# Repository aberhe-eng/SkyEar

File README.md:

# SkyEar

**A pocket radio that listens to lightning thousands of miles away.**

Lightning strikes somewhere on Earth dozens of times every second, and every strike gives off a burst of very-low-frequency (VLF) radio. SkyEar picks those bursts up with a wire antenna, cleans them up, and plays them through headphones. You hear distant storms as crackling ("sferics"), and sometimes as eerie falling whistles ("whistlers"): lightning signals that went out into space, followed Earth's magnetic field, and came back down.

I'm building it for [Hack Club Half Life](https://halflife.hackclub.com) (Week 1: PCB design).

## How it works

SkyEar is a fully analog circuit: two op-amp chips, one headphone amp chip, and a 9 V battery. The signal goes through it in this order:

| Stage | Part | What it does |
| --- | --- | --- |
| Antenna input | J2, R4, D3, D4 | A wire antenna plus a ground stake. The diodes dump static from the antenna safely into the power rails. |
| Buffer | U1A (TL072), R5 = 10 MΩ | A short antenna acts like a tiny capacitor (~10–30 pF), so it can barely push any current. The 10 MΩ input and a JFET op-amp copy the signal without draining it. |
| Hum filter | U1B, C6, C7, R6, R7 | 2nd-order high-pass at ~625 Hz. Power lines put out 60 Hz hum that's way louder than lightning on another continent, so this cuts it. |
| Gain | U2A, R8, R9 | Amplifies by 1 + 100k / 3.3k ≈ 31. |
| High-frequency filter | U2B, R10, R11, C10, C11 | 2nd-order low-pass at ~10.7 kHz. Cuts hiss, AM radio, and the Navy's VLF transmitters (~20–25 kHz). |
| Headphone amp | U3 (LM386), RV1 | Another 20x, with a volume knob. About 620x total from antenna to ears. |
| Line out | J4 | A clean copy of the audio for recording, or for my later Half Life projects. |
| Power | J1, SW1, D1, R2, R3 | 9 V battery with reverse-polarity protection. R2/R3 make a ~4.35 V "virtual ground" (VREF) so the op-amps can swing both ways on one battery. |

The filter cutoffs come from the standard formulas:

- Input: f = 1 / (2π · 10 MΩ · 30 pF) ≈ 530 Hz
- Hum filter: f = 1 / (2π · 10 nF · √(18 kΩ · 36 kΩ)) ≈ 625 Hz
- Low-pass: f = 1 / (2π · 10 kΩ · √(2.2 nF · 1 nF)) ≈ 10.7 kHz

## Schematic

The full KiCad project is in [`pcb/`](pcb/). Open `pcb/skyear.kicad_pro` in KiCad 10 (the schematic alone also opens in KiCad 8 and 9). A PDF copy is at [`pcb/skyear_schematic.pdf`](pcb/skyear_schematic.pdf).

### Block by block

**Power:** 9 V battery → slide switch → 1N5817 Schottky diode (blocks a backwards battery, only ~0.3 V drop) → +9V rail, with a power LED.

**Virtual ground:** two 10k resistors split the battery to ~4.35 V so every op-amp signal can swing above and below it.

**Antenna input + buffer:** R5 is 10 MΩ so the antenna's tiny signal isn't loaded down, and U1A just copies it.

C5 (22 pF) is marked "do not fit". It only gets soldered if AM radio leaks in.

**Hum filter:** R7 (36k) is exactly twice R6 (18k), which gives a flat Butterworth response with no bump at the cutoff.

**Gain stage:** x31. C9 keeps DC from being amplified and C8 starts rolling off the highs.

**High-frequency filter:** cuts everything above ~10.7 kHz.

**Line out:** a DC-blocked copy of the audio on a 2-pin header.

**Headphone amp:** LM386 at x20. R14 + C17 keep it from oscillating, C18 blocks DC from the headphones, and R15 limits the max volume. Tip and ring are tied together so both ears get the signal.

### Checks

KiCad's Electrical Rules Checker: **0 errors**. The 2 warnings are KiCad 10 noticing that the LED and potentiometer symbols have newer artwork in its library; the pins are identical.

Every part has a footprint assigned:

+9V and GND are in a "Power" net class so they get thicker 0.6 mm tracks on the PCB (signals get 0.3 mm):

## PCB

| | |
| --- | --- |
| Size | 90 × 64 mm, 2 layers, 1.6 mm FR-4, 4 × M3 mounting holes |
| Tracks | 0.3 mm signal, 0.6 mm for +9V and GND, 0.25 mm clearance |
| Ground | GND pour on both layers, stitched together with vias |
| Checks | KiCad DRC: **0 errors, 0 unconnected pads, 0 schematic mismatches** ([report](pcb/skyear_drc_report.rpt)) |

The 14 DRC warnings are all expected: 13 are connector bodies (terminal blocks, switch, jack, LED) that hang over the board edge on purpose, and 1 is the headphone jack footprint, whose pin slots were widened from 0.4 mm to 0.6 mm because JLCPCB can't make plated slots narrower than 0.5 mm.

### Layout

- **Signal flows left to right.** Antenna in on the left edge, then the buffer (U1), hum filter, gain stage (U2) and low-pass filter across the top. The headphone amp (U3), volume knob and jack are along the bottom right.
- **The antenna input is kept tiny.** Everything touching the 10 MΩ input node (R4, R5, D3, D4, C5) sits right next to U1 pin 3, because that node picks up hum if its traces are long.
- **The headphone amp is far from the input.** The LM386's output (the loudest signal on the board) is in the opposite corner from the antenna, so it can't feed back into the input and squeal.
- **Every chip has its 100 nF decoupling cap next to its power pin** (C19 for U1, C20 for U2, C15 for U3).
- **Controls are on the edges.** Battery and antenna terminals on the left, power switch and volume on the bottom, headphone jack and line out on the right.
- Routed with [Freerouting](https://github.com/freerouting/freerouting), then GND pours on both layers.

| Front copper | Back copper |
| --- | --- |
|  |  |

The front/back images are rendered straight from the Gerber files, so they show exactly what gets manufactured. The 3D views are from KiCad; the volume pot has no 3D model in KiCad's library, so only its pads show.

### Ordering the boards

[`pcb/skyear_gerbers_jlcpcb.zip`](pcb/skyear_gerbers_jlcpcb.zip) is ready to upload at [jlcpcb.com/quote](https://jlcpcb.com/quote) (2 layers, 1.6 mm, 5 pcs, any color). The individual Gerber and drill files are in [`pcb/gerbers/`](pcb/gerbers/). The board file is `pcb/skyear.kicad_pcb` (KiCad 10).

## Specs

| | |
| --- | --- |
| Frequency range | ~600 Hz to ~10.7 kHz |
| Power | One 9 V battery, ~10–15 mA |
| Input | Wire antenna + ground stake, 10 MΩ input resistance |
| Outputs | 3.5 mm headphones (with volume), 2-pin line out |
| Parts | 100% through-hole, all chips socketed |
| Board | 2 layers, 90 × 64 mm, 4 × M3 mounting holes |

## Parts list

[`bom.csv`](bom.csv) has every part with its quantity, real DigiKey price and part number, plus the PCBs from JLCPCB.

- Parts from DigiKey: **$29.67** (34 lines, including spares of the cheap parts)
- 5 PCBs from JLCPCB: **$2.00**
- **Parts total: $31.67**, before tax and shipping. That's inside the Tier 2 budget ($65).

Not on the list: a 9 V battery (any store) and the antenna wire + ground stake (already owned).

There's no firmware: SkyEar is entirely analog.

## Status

- [x] Circuit design and filter math
- [x] Schematic (KiCad), 0 errors in the electrical rules check
- [x] Price the BOM (Tier 2)
- [x] PCB layout and routing, 0 DRC errors
- [x] Gerber files for fabrication
- [ ] Build week: solder and test
- [ ] Field test: record real sferics and post the audio here

## Safety

- **Never set up the antenna when there are storms nearby.** If you can hear thunder, pack up. SkyEar listens to lightning far away, never close.
- **Battery power only.** Never connect it to a wall adapter.
- **Turn the volume to zero before putting headphones on.**
- Keep antennas far away from overhead power lines.

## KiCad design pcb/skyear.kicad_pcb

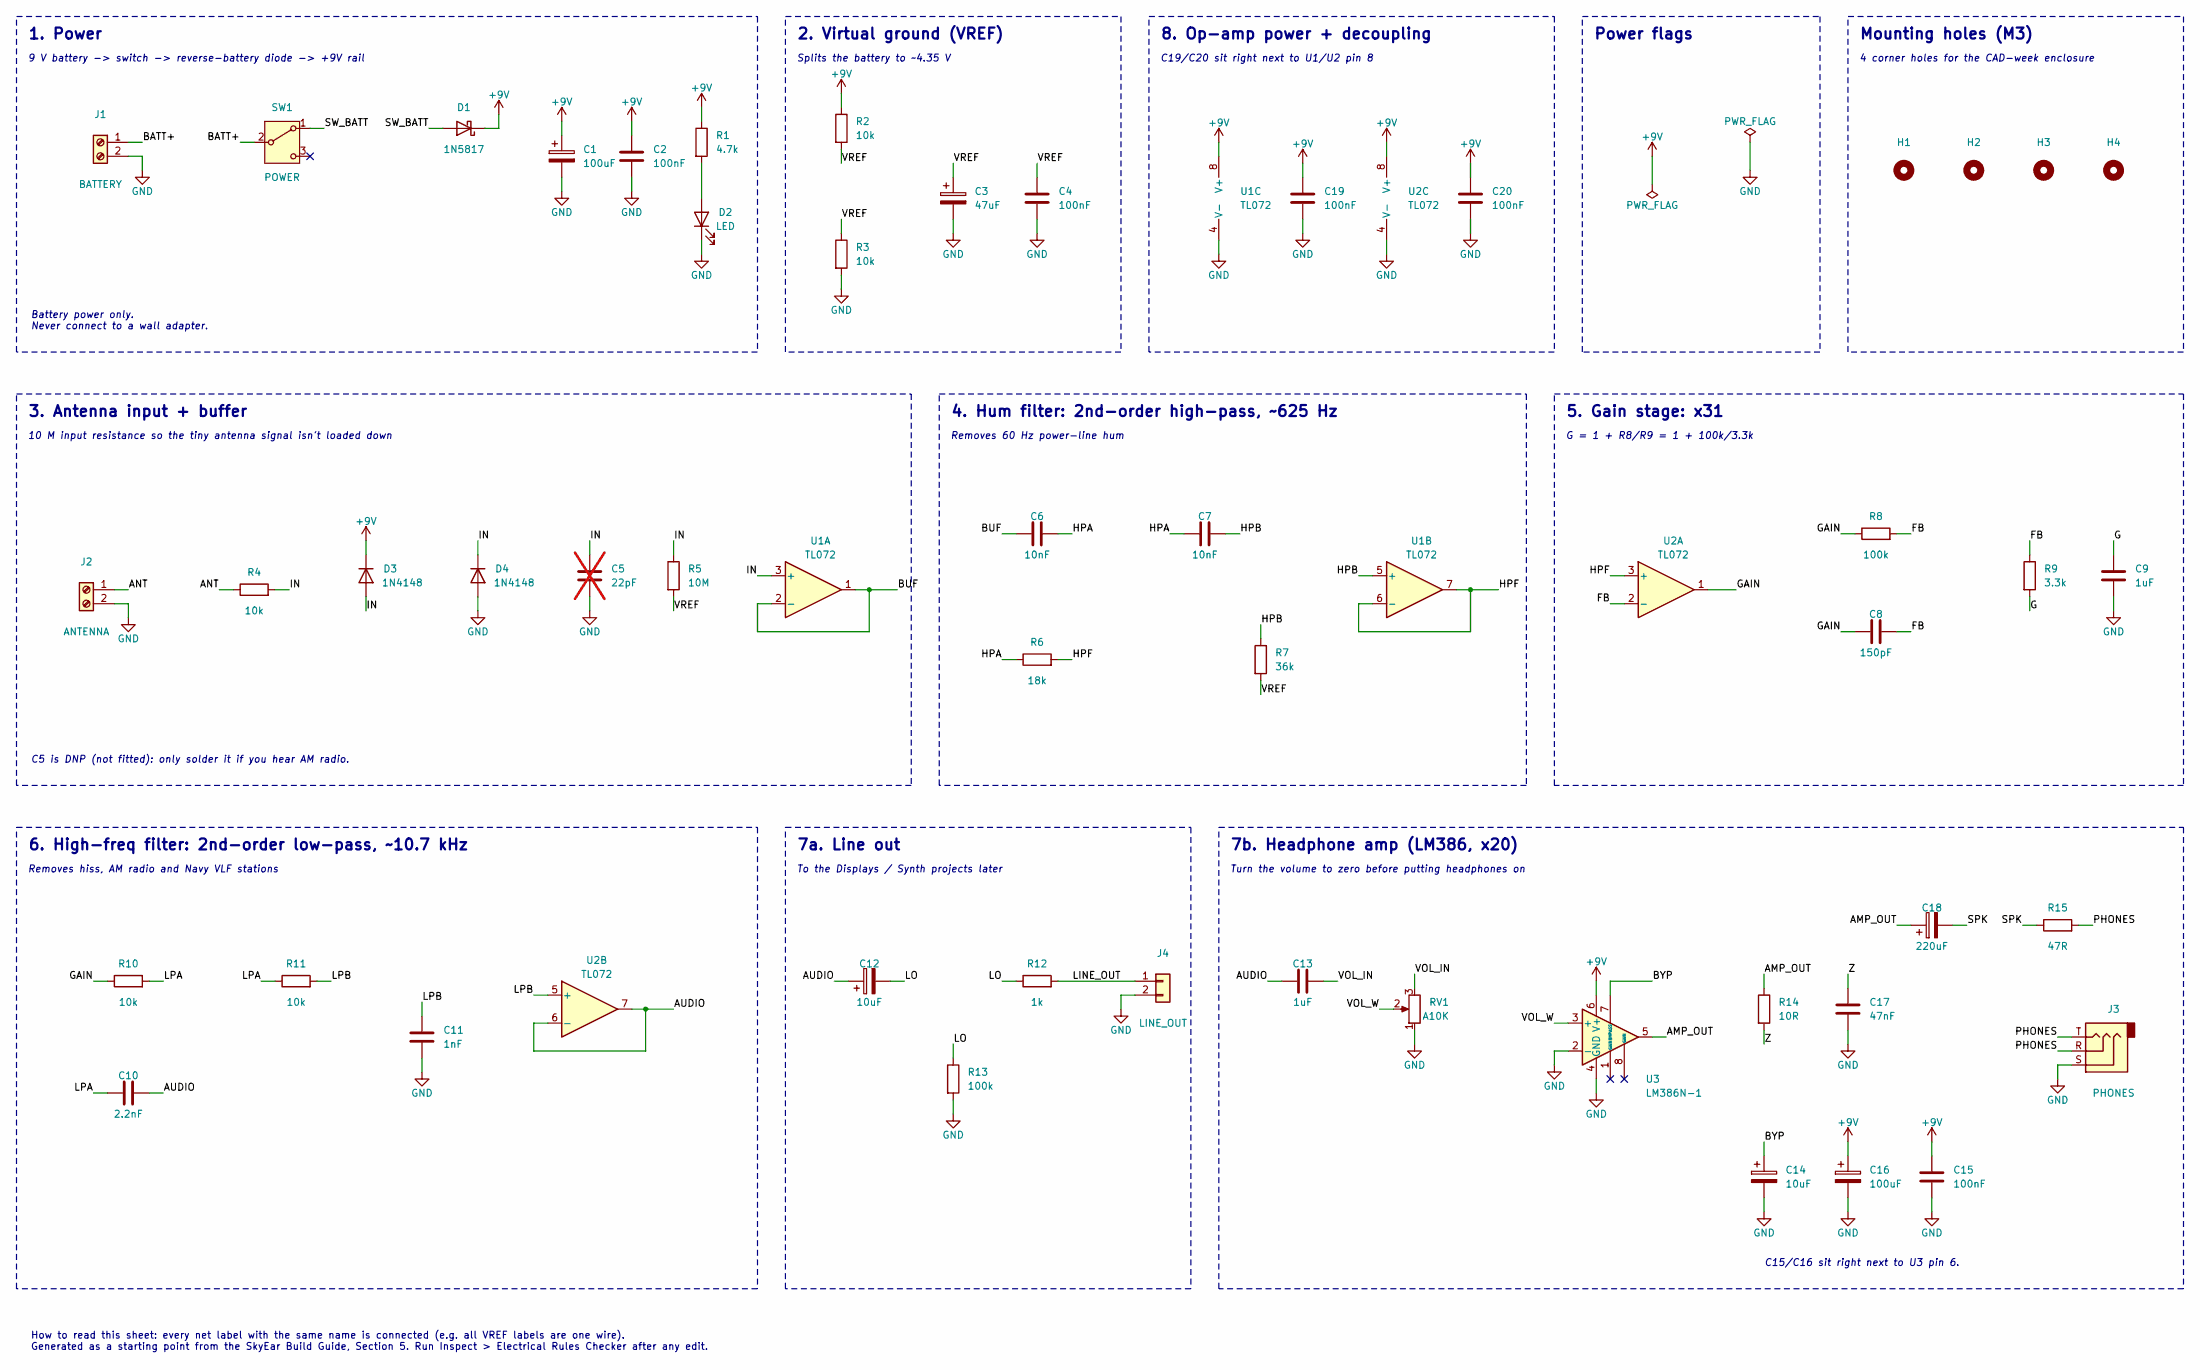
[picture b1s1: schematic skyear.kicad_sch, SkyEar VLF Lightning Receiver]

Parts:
C1, C16: 100uF; CP_Radial_D6.3mm_P2.50mm
C2, C4, C15, C19, C20: 100nF; C_Disc_D5.0mm_W2.5mm_P5.00mm
C3: 47uF; CP_Radial_D6.3mm_P2.50mm
C5: 22pF; C_Disc_D5.0mm_W2.5mm_P5.00mm; not fitted
C6, C7: 10nF; C_Disc_D5.0mm_W2.5mm_P5.00mm
C8: 150pF; C_Disc_D5.0mm_W2.5mm_P5.00mm
C9, C13: 1uF; C_Disc_D5.0mm_W2.5mm_P5.00mm
C10: 2.2nF; C_Disc_D5.0mm_W2.5mm_P5.00mm
C11: 1nF; C_Disc_D5.0mm_W2.5mm_P5.00mm
C12, C14: 10uF; CP_Radial_D5.0mm_P2.00mm
C17: 47nF; C_Disc_D5.0mm_W2.5mm_P5.00mm
C18: 220uF; CP_Radial_D8.0mm_P3.50mm
D1: 1N5817; D_DO-41_SOD81_P10.16mm_Horizontal
D2: LED; LED_D5.0mm
D3, D4: 1N4148; D_DO-35_SOD27_P7.62mm_Horizontal
H1, H2, H3, H4: MountingHole; MountingHole_3.2mm_M3
J1: BATTERY; TerminalBlock_Phoenix_MKDS-1,5-2-5.08_1x02_P5.08mm_Horizont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; MPN Phoenix MKDS 1,5/2-5,08 (or same 5.08 m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
J2: ANTENNA; TerminalBlock_Phoenix_MKDS-1,5-2-5.08_1x02_P5.08mm_Horizont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; MPN Phoenix MKDS 1,5/2-5,08 (or same 5.08 m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
J3: PHONES; Jack_3.5mm_CUI_SJ1-3523N_Horizontal; MPN CUI SJ1-3523N
J4: LINE_OUT; PinHeader_1x02_P2.54mm_Vertical
R1: 4.7k; R_Axial_DIN0207_L6.3mm_D2.5mm_P10.16mm_Horizontal
R2, R3, R4, R10, R11: 10k; R_Axial_DIN0207_L6.3mm_D2.5mm_P10.16mm_Horizontal
R5: 10M; R_Axial_DIN0207_L6.3mm_D2.5mm_P10.16mm_Horizontal
R6: 18k; R_Axial_DIN0207_L6.3mm_D2.5mm_P10.16mm_Horizontal
R7: 36k; R_Axial_DIN0207_L6.3mm_D2.5mm_P10.16mm_Horizontal
R8, R13: 100k; R_Axial_DIN0207_L6.3mm_D2.5mm_P10.16mm_Horizontal
R9: 3.3k; R_Axial_DIN0207_L6.3mm_D2.5mm_P10.16mm_Horizontal
R12: 1k; R_Axial_DIN0207_L6.3mm_D2.5mm_P10.16mm_Horizontal
R14: 10R; R_Axial_DIN0207_L6.3mm_D2.5mm_P10.16mm_Horizontal
R15: 47R; R_Axial_DIN0207_L6.3mm_D2.5mm_P10.16mm_Horizontal
RV1: A10K; Potentiometer_Alps_RK09K_Single_Vertical; MPN Alps RK09K series, 10k audio (A) taper
SW1: POWER; SW_Slide_SPDT_Angled_CK_OS102011MA1Q; MPN C&K OS102011MA1QN1 (right-angle)
U1, U2: TL072; DIP-8_W7.62mm_Socket
U3: LM386N-1; DIP-8_W7.62mm_Socket

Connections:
+9V: C1.1, C2.1, C15.1, C16.1, C19.1, C20.1, D1.1 (K), D3.1 (K), R1.1, R2.1, U1.8 (V+), U2.8 (V+), U3.6 (V+)
/AMP_OUT: C18.1, R14.1, U3.5
/ANT: J2.1, R4.1
/AUDIO: C10.2, C12.1, C13.1, U2.6 (-), U2.7
/BATT+: J1.1, SW1.2 (B)
/BUF: C6.1, U1.1, U1.2 (-)
/BYP: C14.1, U3.7 (BYPASS)
/FB: C8.2, R8.2, R9.1, U2.2 (-)
/G: C9.1, R9.2
/GAIN: C8.1, R8.1, R10.1, U2.1
/HPA: C6.2, C7.1, R6.1
/HPB: C7.2, R7.1, U1.5 (+)
/HPF: R6.2, U1.6 (-), U1.7, U2.3 (+)
/IN: C5.1, D3.2 (A), D4.1 (K), R4.2, R5.1, U1.3 (+)
/LINE_OUT: J4.1, R12.2
/LO: C12.2, R12.1, R13.1
/LPA: C10.1, R10.2, R11.1
/LPB: C11.1, R11.2, U2.5 (+)
/PHONES: J3.R, J3.T, R15.2
/SPK: C18.2, R15.1
/SW_BATT: D1.2 (A), SW1.1 (A)
/VOL_IN: C13.2, RV1.3
/VOL_W: RV1.2, U3.3 (+)
/VREF: C3.1, C4.1, R2.2, R3.1, R5.2, R7.2
/Z: C17.1, R14.2
GND: C1.2, C2.2, C3.2, C4.2, C5.2, C9.2, C11.2, C14.2, C15.2, C16.2, C17.2, C19.2, C20.2, D2.1 (K), D4.2 (A), J1.2, J2.2, J3.S, J4.2, R3.2, R13.2, RV1.1, U1.4 (V-), U2.4 (V-), U3.2 (-), U3.4 (GND)
unnamed: D2.2 (A), R1.2

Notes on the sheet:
1. Power
9 V battery -> switch -> reverse-battery diode -> +9V rail
Battery power only. Never connect to a wall adapter.
2. Virtual ground (VREF)
Splits the battery to ~4.35 V
8. Op-amp power + decoupling
C19/C20 sit right next to U1/U2 pin 8
Power flags
Mounting holes (M3)
4 corner holes for the CAD-week enclosure
3. Antenna input + buffer
10 M input resistance so the tiny antenna signal isn't loaded down
C5 is DNP (not fitted): only solder it if you hear AM radio.
4. Hum filter: 2nd-order high-pass, ~625 Hz
Removes 60 Hz power-line hum
5. Gain stage: x31
G = 1 + R8/R9 = 1 + 100k/3.3k
6. High-freq filter: 2nd-order low-pass, ~10.7 kHz
Removes hiss, AM radio and Navy VLF stations
7a. Line out
To the Displays / Synth projects later
7b. Headphone amp (LM386, x20)
Turn the volume to zero before putting headphones on
C15/C16 sit right next to U3 pin 6.
How to read this sheet: every net label with the same name is connected (e.g. all VREF labels are one wire). Generated as a starting point from the SkyEar Build Guide, Section 5. Run Inspect > Electrical Rules Checker after any edit.

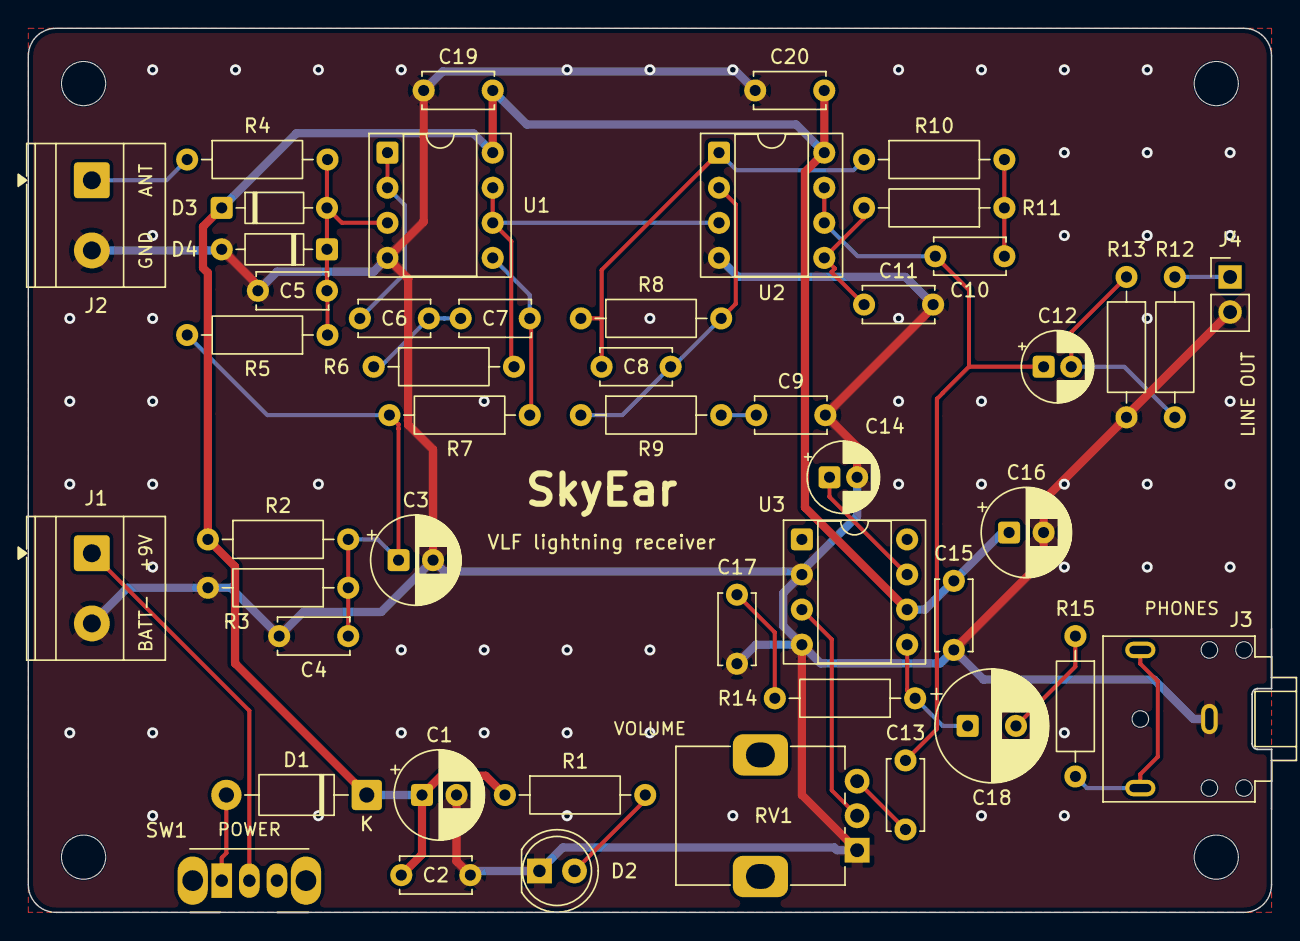
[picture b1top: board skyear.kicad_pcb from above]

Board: 2 copper layers, 90.0 x 64.0 mm, 52 parts (0 on the bottom side), 27 nets.

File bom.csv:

Part,Qty,Unit price (USD),Total (USD),Vendor,Link,Refs,Manufacturer,MPN,Vendor PN
Resistor 4.7k ohm 1/4W - YAGEO MFR-25FBF52-4K7,2,0.11,0.22,DigiKey,https://www.digikey.com/en/products/result?keywords=MFR-25FB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,R1,YAGEO,MFR-25FBF52-4K7,MFR-25FBF52-4K7-ND
Resistor 10k ohm 1/4W - YAGEO MFR-25FBF52-10K,10,0.042,0.42,DigiKey,https://www.digikey.com/en/products/result?keywords=10.0KXBK-ND,"R2,R3,R4,R10,R11",YAGEO,MFR-25FBF52-10K,10.0KXBK-ND
Resistor 10M ohm (10 megohm) 1/4W - Stackpole CF14JT10M0,2,0.10,0.20,DigiKey,https://www.digikey.com/en/products/result?keywords=CF14JT10M0CT-ND,R5,Stackpole,CF14JT10M0,CF14JT10M0CT-ND
Resistor 18k ohm 1/4W - YAGEO MFR-25FBF52-18K,2,0.10,0.20,DigiKey,https://www.digikey.com/en/products/result?keywords=MFR-25FB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,R6,YAGEO,MFR-25FBF52-18K,MFR-25FBF52-18K-ND
Resistor 36k ohm 1/4W - YAGEO MFR-25FBF52-36K,2,0.10,0.20,DigiKey,https://www.digikey.com/en/products/result?keywords=13-MFR-2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,R7,YAGEO,MFR-25FBF52-36K,13-MFR-25FBF52-36K-ND
Resistor 100k ohm 1/4W - YAGEO MFR-25FBF52-100K,3,0.10,0.30,DigiKey,https://www.digikey.com/en/products/result?keywords=100KXBK-ND,"R8,R13",YAGEO,MFR-25FBF52-100K,100KXBK-ND
Resistor 3.3k ohm 1/4W - YAGEO MFR-25FBF52-3K3,2,0.10,0.20,DigiKey,https://www.digikey.com/en/products/result?keywords=MFR-25FB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,R9,YAGEO,MFR-25FBF52-3K3,MFR-25FBF52-3K3-ND
Resistor 1k ohm 1/4W - YAGEO MFR-25FBF52-1K,2,0.10,0.20,DigiKey,https://www.digikey.com/en/products/result?keywords=1.00KXBK-ND,R12,YAGEO,MFR-25FBF52-1K,1.00KXBK-ND
Resistor 10 ohm 1/4W - YAGEO MFR-25FBF52-10R,2,0.10,0.20,DigiKey,https://www.digikey.com/en/products/result?keywords=10.0XBK-ND,R14,YAGEO,MFR-25FBF52-10R,10.0XBK-ND
Resistor 47 ohm 1/4W - YAGEO MFR-25FBF52-47R,2,0.10,0.20,DigiKey,https://www.digikey.com/en/products/result?keywords=MFR-25FB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,R15,YAGEO,MFR-25FBF52-47R,MFR-25FBF52-47R-ND
Electrolytic capacitor 100uF 25V - Panasonic ECA-1EM101I,3,0.35,1.05,DigiKey,https://www.digikey.com/en/products/result?keywords=10-ECA-1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,"C1,C16",Panasonic,ECA-1EM101I,10-ECA-1EM101ICT-ND
Ceramic capacitor 100nF 50V - TDK FG28X7R1H104KNT00,10,0.135,1.35,DigiKey,https://www.digikey.com/en/products/result?keywords=445-FG28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,"C2,C4,C15,C19,C20",TDK,FG28X7R1H104KNT00,445-FG28X7R1H104KNT00-ND
Electrolytic capacitor 47uF 50V - Panasonic ECA-1HM470,2,0.33,0.66,DigiKey,https://www.digikey.com/en/products/result?keywords=P5181-ND,C3,Panasonic,ECA-1HM470,P5181-ND
"Ceramic capacitor 22pF 100V (C5 spare, not fitted) - TDK FG28C0G2A220JNT00",1,0.26,0.26,DigiKey,https://www.digikey.com/en/products/result?keywords=445-175549-ND,C5,TDK,FG28C0G2A220JNT00,445-175549-ND
Ceramic capacitor 10nF 50V C0G - TDK FG28C0G1H103JNT00,3,0.35,1.05,DigiKey,https://www.digikey.com/en/products/result?keywords=FG28C0G1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,"C6,C7",TDK,FG28C0G1H103JNT00,FG28C0G1H103JNT00-ND
Ceramic capacitor 150pF 50V C0G - TDK FG28C0G1H151JNT00,2,0.22,0.44,DigiKey,https://www.digikey.com/en/products/result?keywords=445-181753-ND,C8,TDK,FG28C0G1H151JNT00,445-181753-ND
Ceramic capacitor 1uF 25V - TDK FG28X7R1E105KRT00,3,0.31,0.93,DigiKey,https://www.digikey.com/en/products/result?keywords=445-181761-ND,"C9,C13",TDK,FG28X7R1E105KRT00,445-181761-ND
Ceramic capacitor 2.2nF 50V C0G - TDK FG28C0G1H222JNT00,2,0.27,0.54,DigiKey,https://www.digikey.com/en/products/result?keywords=445-FG28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,C10,TDK,FG28C0G1H222JNT00,445-FG28C0G1H222JNT00-ND
Ceramic capacitor 1nF 50V C0G - TDK FG28C0G1H102JNT00,2,0.25,0.50,DigiKey,https://www.digikey.com/en/products/result?keywords=445-FG28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,C11,TDK,FG28C0G1H102JNT00,445-FG28C0G1H102JNT00-ND
Electrolytic capacitor 10uF 50V - KEMET ESK106M050AC3AA,3,0.19,0.57,DigiKey,https://www.digikey.com/en/products/result?keywords=399-6599-ND,"C12,C14",KEMET,ESK106M050AC3AA,399-6599-ND
Ceramic capacitor 47nF 50V - TDK FG28X7R1H473KNT00,2,0.23,0.46,DigiKey,https://www.digikey.com/en/products/result?keywords=445-FG28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,C17,TDK,FG28X7R1H473KNT00,445-FG28X7R1H473KNT00-ND
Electrolytic capacitor 220uF 25V - Nichicon UVZ1E221MPD,2,0.44,0.88,DigiKey,https://www.digikey.com/en/products/result?keywords=493-1302-ND,C18,Nichicon,UVZ1E221MPD,493-1302-ND
Schottky diode 1N5817 (reverse-battery protection) - onsemi 1N5817G,2,0.67,1.34,DigiKey,https://www.digikey.com/en/products/result?keywords=1N5817GOS-ND,D1,onsemi,1N5817G,1N5817GOS-ND
Red 5 mm LED (power light) - Kingbright WP7113ID,2,0.21,0.42,DigiKey,https://www.digikey.com/en/products/result?keywords=754-1264-ND,D2,Kingbright,WP7113ID,754-1264-ND
Diode 1N4148 (antenna input protection) - onsemi 1N4148,4,0.10,0.40,DigiKey,https://www.digikey.com/en/products/result?keywords=1N4148FS-ND,"D3,D4",onsemi,1N4148,1N4148FS-ND
"TL072 dual JFET op-amp, DIP-8 - Texas Instruments TL072ACP",3,1.50,4.50,DigiKey,https://www.digikey.com/en/products/result?keywords=296-7190-5-ND,"U1,U2",Texas Instruments,TL072ACP,296-7190-5-ND
"LM386 headphone amplifier, DIP-8 - Texas Instruments LM386N-1/NOPB",2,1.18,2.36,DigiKey,https://www.digikey.com/en/products/result?keywords=296-44414-5-ND,U3,Texas Instruments,LM386N-1/NOPB,296-44414-5-ND
"2-pin screw terminal 5.08 mm (battery, antenna) - Phoenix Contact 1715721",2,1.16,2.32,DigiKey,https://www.digikey.com/en/products/result?keywords=277-1263-ND,"J1,J2",Phoenix Contact,1715721,277-1263-ND
3.5 mm headphone jack - Same Sky (CUI) SJ1-3523N,1,1.12,1.12,DigiKey,https://www.digikey.com/en/products/result?keywords=CP1-3523N-ND,J3,Same Sky (CUI),SJ1-3523N,CP1-3523N-ND
2-pin header 2.54 mm (line out) - Sullins PREC002SAAN-RC,1,0.10,0.10,DigiKey,https://www.digikey.com/en/products/result?keywords=35-PREC0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,J4,Sullins,PREC002SAAN-RC,35-PREC002SAAN-RC-ND
Slide switch SPDT right-angle (power) - C&K OS102011MA1QN1,1,0.75,0.75,DigiKey,https://www.digikey.com/en/products/result?keywords=CKN9559-ND,SW1,C&K,OS102011MA1QN1,CKN9559-ND
10k potentiometer (volume) - Alps Alpine RK09K1130AP5,1,1.70,1.70,DigiKey,https://www.digikey.com/en/products/result?keywords=4809-RK0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,RV1,Alps Alpine,RK09K1130AP5,4809-RK09K1130AP5-ND
9V battery snap clip - Keystone 232,1,0.66,0.66,DigiKey,https://www.digikey.com/en/products/result?keywords=36-232-ND,J1,Keystone,232,36-232-ND
DIP-8 IC socket - Mill-Max 110-44-308-41-001000,3,0.99,2.97,DigiKey,https://www.digikey.com/en/products/result?keywords=ED90048-ND,U1-U3,Mill-Max,110-44-308-41-001000,ED90048-ND
"SkyEar PCB v1.0: 2-layer FR-4, 1.6 mm, 90 x 64 mm (Gerbers in pcb/gerbers)",5,0.40,2.00,JLCPCB,https://jlcpcb.com/quote,PCB,JLCPCB,,
